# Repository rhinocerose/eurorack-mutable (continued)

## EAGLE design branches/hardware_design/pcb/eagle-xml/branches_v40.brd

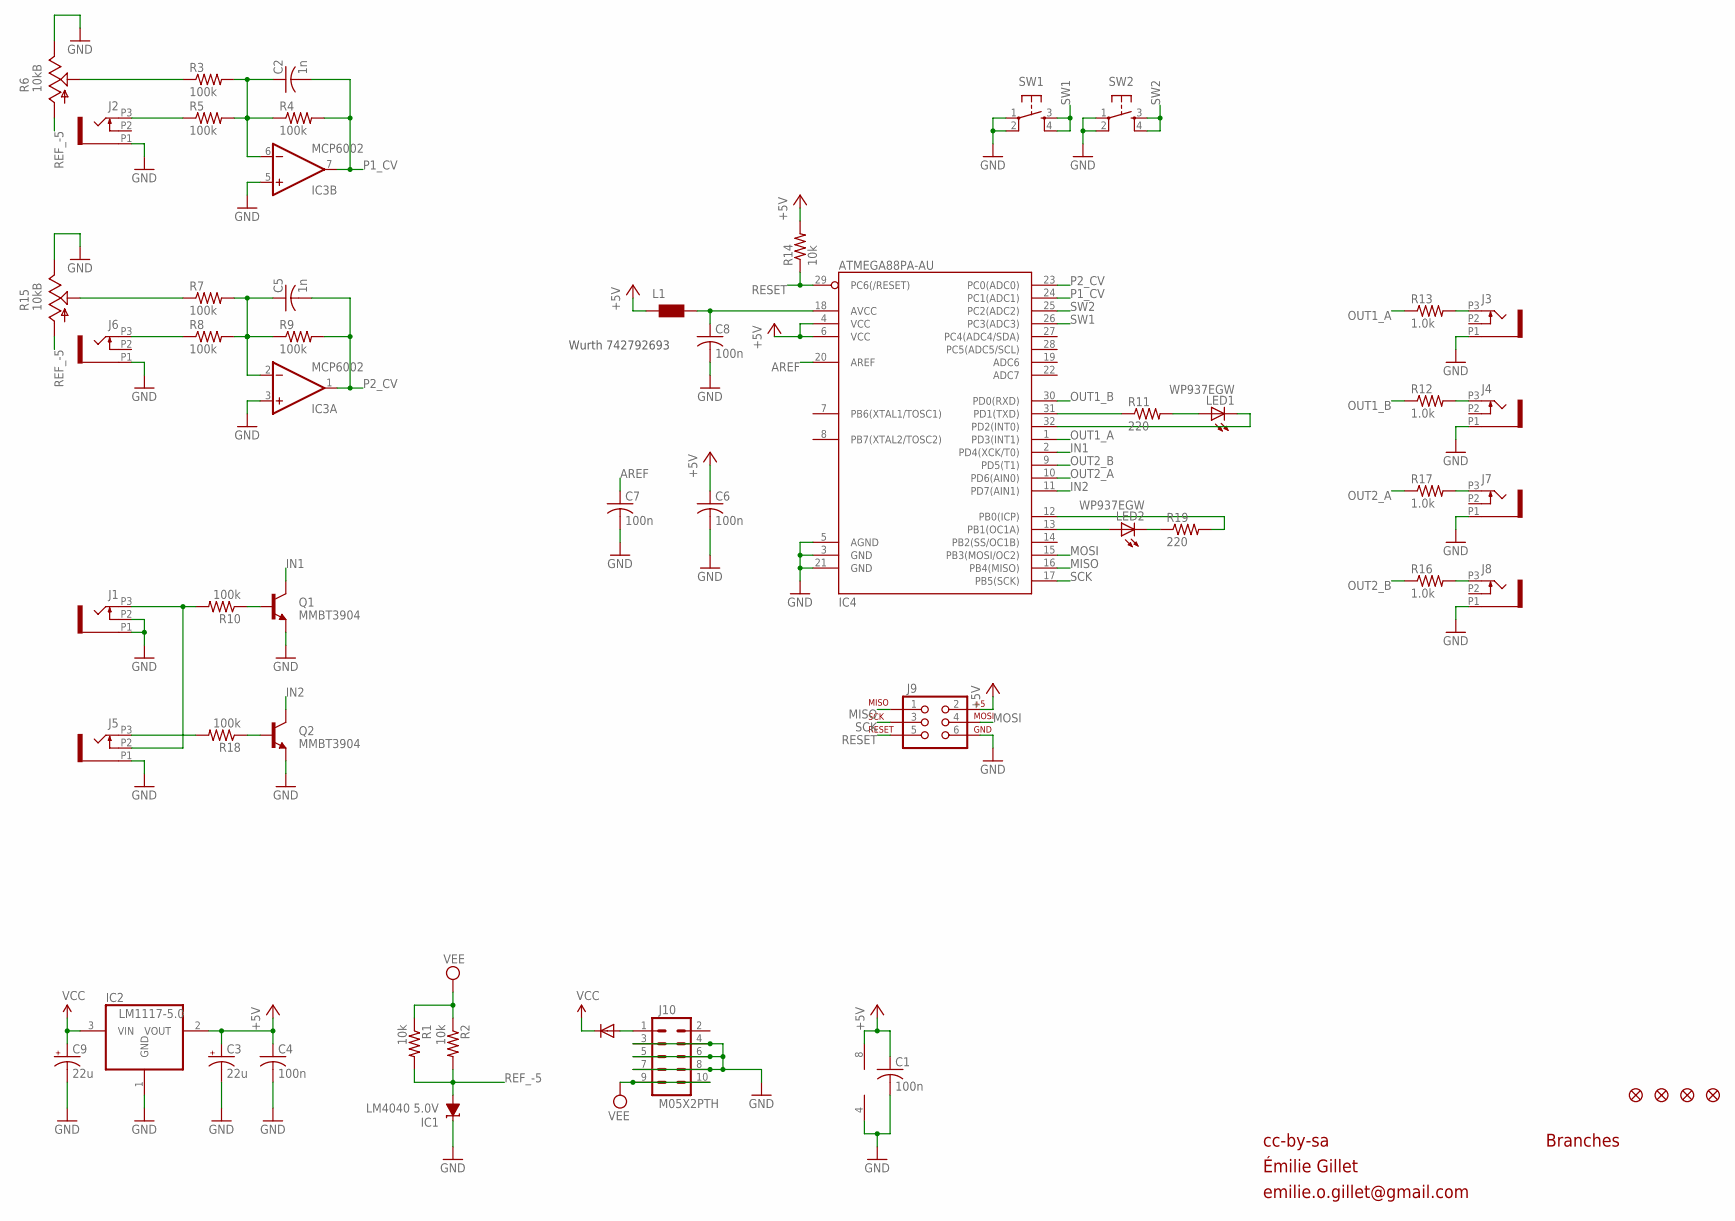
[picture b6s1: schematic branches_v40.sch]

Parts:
C1, C4, C6, C7, C8: 100n; C0603
C2, C5: 1n; C0603
C3, C9: 22u; PANASONIC_C
D1: 1N5819HW; SOD123
F1, F2, F3, F4: FIDUCIAL1X2; FIDUCIAL-1X2
IC1: LM4040 5.0V; DBZ_R-PDSO-G3
IC2: LM1117-5.0; SOT223
IC3: MCP6002; SO08
IC4: ATMEGA88PA-AU; TQFP32-08
J1, J2, J3, J4, J5, J6, J7, J8: PJ301_THONKICONN6; WQP_PJ_301M6
J9: AVR_SPI_PRG_6PTH; 2X3
J10: M05X2PTH; AVR_ICSP
L1: WE-CBF_0603; 0603
LED1, LED2: WP937EGW; LED3MM
Q1, Q2: MMBT3904; SOT23-BEC
R1, R2, R14: 10k; R0603
R3, R4, R5, R7, R8, R9, R10, R18: 100k; R0603
R6, R15: 10kB; ALPS_POT_VERTICAL_PS
R11, R19: 220; R0603
R12, R13, R16, R17: 1.0k; R0603
SW1, SW2: TAC_SWITCHPTH; TACTILE-PTH

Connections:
+5V: C1.1, C3.+, C4.1, C6.1, IC2.2 (VOUT), IC3.8 (V+), IC4.4 (VCC), IC4.6 (VCC), J9.2, L1.1, R14.2
AREF: C7.1, IC4.20 (AREF)
GATE1_IN: J1.P3 (3), J5.P2 (2), R10.2
GATE2_IN: J5.P3 (3), R18.2
GND: C1.2, C3.-, C4.2, C6.2, C7.2, C8.2, C9.-, IC1.1 (C), IC2.1 (GND), IC3.3 (+IN), IC3.4 (V-), IC3.5 (+IN), IC4.3 (GND), IC4.5 (AGND), IC4.21 (GND), J1.P1 (1), J1.P2 (2), J2.P1 (1), J3.P1 (1), J4.P1 (1), J5.P1 (1), J6.P1 (1), J7.P1 (1), J8.P1 (1), J9.6, J10.3, J10.4, J10.5, J10.6, J10.7, J10.8, Q1.E, Q2.E, R6.P$1 (E), R15.P$1 (E), SW1.1, SW1.2, SW2.1, SW2.2
IN1: IC4.2 (PD4(XCK/T0)), Q1.C
IN2: IC4.11 (PD7(AIN1)), Q2.C
MISO: IC4.16 (PB4(MISO)), J9.1
MOSI: IC4.15 (PB3(MOSI/OC2)), J9.4
unnamed: Q1.B, R10.1
unnamed: Q2.B, R18.1
unnamed: D1.A, J10.1
unnamed: C5.1, IC3.2 (-IN), R7.2, R8.2, R9.1
unnamed: J8.P3 (3), R16.2
unnamed: R7.1, R15.P$2 (S)
unnamed: R3.1, R6.P$2 (S)
unnamed: J2.P3 (3), R5.1
unnamed: J6.P3 (3), R8.1
unnamed: IC4.31 (PD1(TXD)), R11.1
unnamed: LED1.A, R11.2
unnamed: IC4.32 (PD2(INT0)), LED1.K (C)
unnamed: IC4.13 (PB1(OC1A)), LED2.A
unnamed: LED2.K (C), R19.1
unnamed: IC4.12 (PB0(ICP)), R19.2
unnamed: C2.1, IC3.6 (-IN), R3.2, R4.1, R5.2
unnamed: J3.P3 (3), R13.2
unnamed: J4.P3 (3), R12.2
unnamed: J7.P3 (3), R17.2
unnamed: C8.1, IC4.18 (AVCC), L1.2
OUT1_A: IC4.1 (PD3(INT1)), R13.1
OUT1_B: IC4.30 (PD0(RXD)), R12.1
OUT2_A: IC4.10 (PD6(AIN0)), R17.1
OUT2_B: IC4.9 (PD5(T1)), R16.1
P1_CV: C2.2, IC3.7 (OUT), IC4.24 (PC1(ADC1)), R4.2
P2_CV: C5.2, IC3.1 (OUT), IC4.23 (PC0(ADC0)), R9.2
REF_-5: IC1.2 (A), R1.2, R2.2, R6.P$3 (A), R15.P$3 (A)
RESET: IC4.29 (PC6(/RESET)), J9.5, R14.1
SCK: IC4.17 (PB5(SCK)), J9.3
SW1: IC4.26 (PC3(ADC3)), SW1.3, SW1.4
SW2: IC4.25 (PC2(ADC2)), SW2.3, SW2.4
VCC: C9.+, D1.C, IC2.3 (VIN)
VEE: J10.9, J10.10, R1.1, R2.1

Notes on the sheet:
cc-by-sa
Branches
Wurth 742792693
Émilie Gillet
emilie.o.gillet@gmail.com

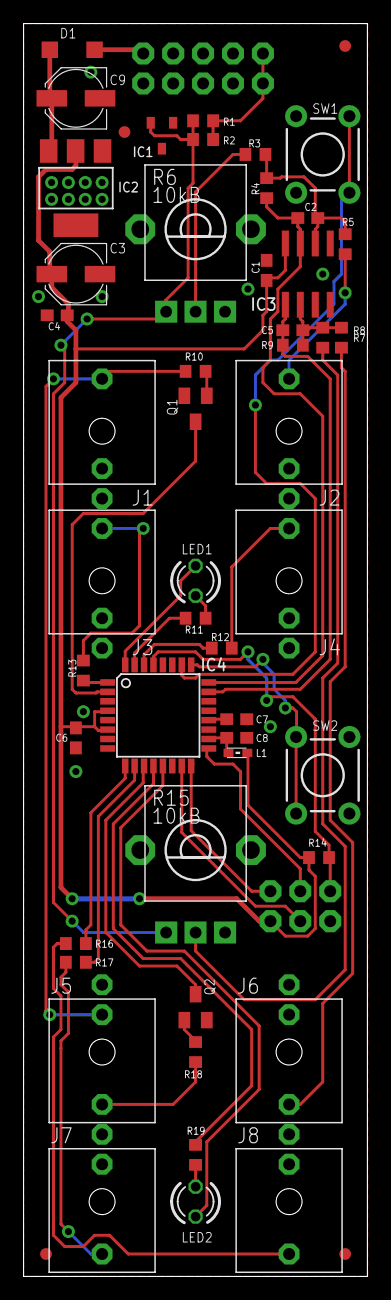
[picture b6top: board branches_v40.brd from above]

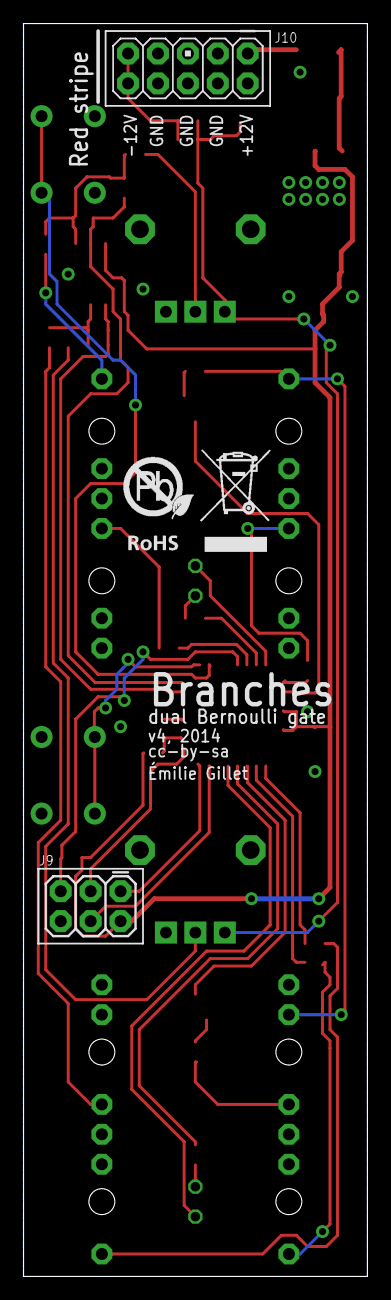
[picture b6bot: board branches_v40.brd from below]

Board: 2 copper layers, 29.2 x 106.4 mm, 55 parts (3 on the bottom side), 42 nets.

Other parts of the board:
U$1: ROHS

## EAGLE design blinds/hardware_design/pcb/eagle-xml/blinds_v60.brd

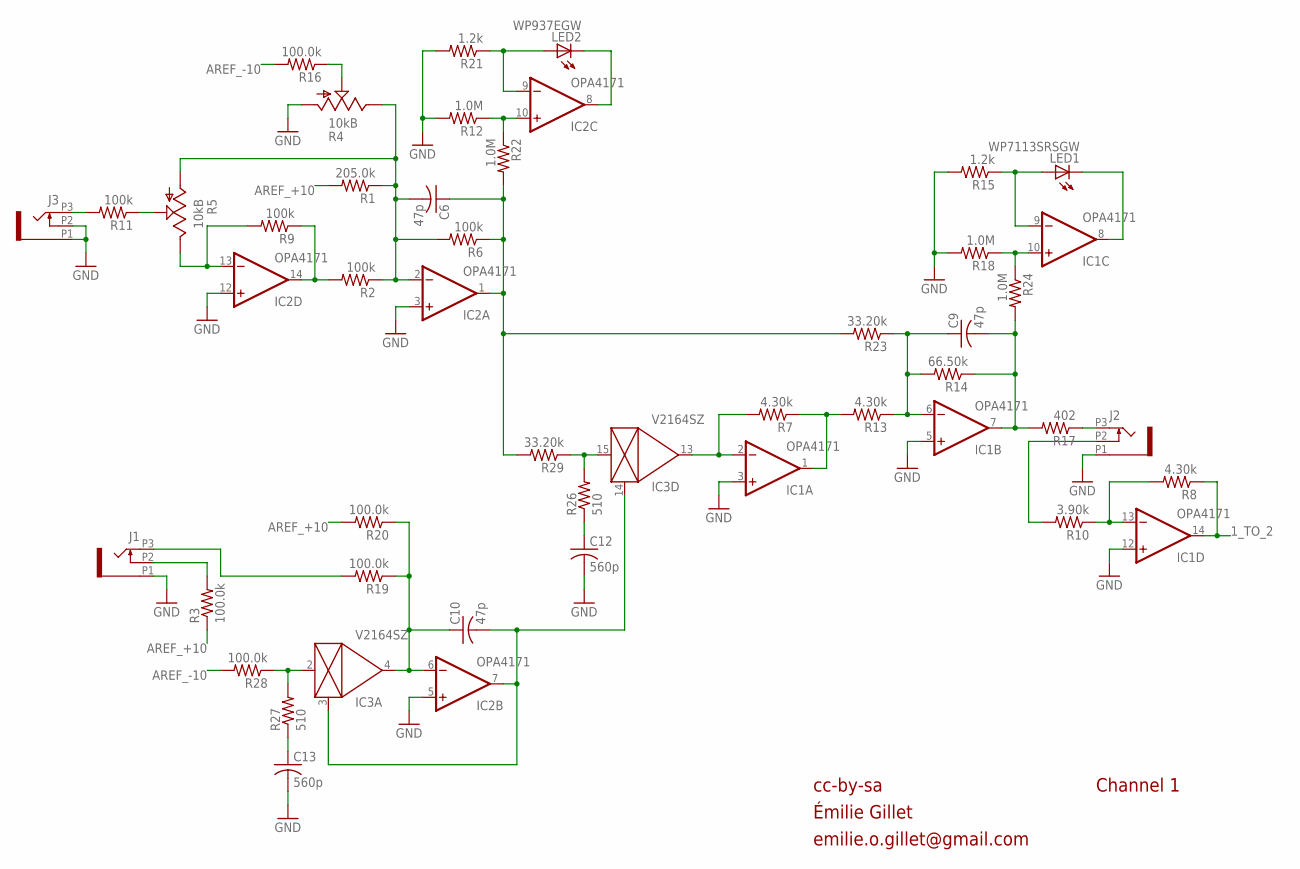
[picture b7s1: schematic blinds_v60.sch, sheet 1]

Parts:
C6, C9, C10: 47p; C0603
C12, C13: 560p; C0603
IC1, IC2: OPA4171; TSSOP14
IC3: V2164SZ; SOIC16N
J1, J2, J3: PJ301_THONKICONN6; WQP_PJ_301M6
LED1: WP7113SRSGW; LED5MM
LED2: WP937EGW; LED3MM
R1: 205.0k; R0603
R2, R6, R9, R11: 100k; R0603
R3, R16, R19, R20, R28: 100.0k; R0603
R4: 10kB; ALPS_POT_VERTICAL_PS
R5: 10kB; ALPS_POT_VERTICAL
R7, R8, R13: 4.30k; R0603
R10: 3.90k; R0603
R12, R18, R22, R24: 1.0M; R0603
R14: 66.50k; R0603
R15, R21: 1.2k; R0603
R17: 402; R0603
R23, R29: 33.20k; R0603
R26, R27: 510; R0603

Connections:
1_TO_2: IC1.14 (OUT), R8.1; also elsewhere on the board
AREF_+10: R1.2, R3.1, R20.2; also elsewhere on the board
AREF_-10: R16.2, R28.2; also elsewhere on the board
CV_IN_1: J3.P3 (3), R11.2
FOO: IC3.2 (IN), R27.2, R28.1
GAIN_1: C6.1, IC2.1 (OUT), R6.1, R22.2, R23.2, R29.2
GND: C12.2, C13.2, IC1.3 (+IN), IC1.5 (+IN), IC1.12 (+IN), IC2.3 (+IN), IC2.5 (+IN), IC2.12 (+IN), J1.P1 (1), J2.P1 (1), J3.P1 (1), J3.P2 (2), R4.P$3 (A), R12.2, R15.2, R18.2, R21.2; also elsewhere on the board
unnamed: R4.P$2 (S), R16.1
unnamed: IC1.2 (-IN), IC3.13 (OUT), R7.2
unnamed: IC2.8 (OUT), LED2.K (C)
unnamed: IC2.13 (-IN), R5.P$1 (E), R9.2
unnamed: J2.P3 (3), R17.1
unnamed: IC2.14 (OUT), R2.2, R9.1
unnamed: C6.2, IC2.2 (-IN), R1.1, R2.1, R4.P$1 (E), R5.P$3 (A), R6.2
unnamed: C9.1, IC1.6 (-IN), R13.1, R14.2, R23.1
unnamed: R5.P$2 (S), R11.1
unnamed: IC2.9 (-IN), LED2.A, R21.1
unnamed: IC1.8 (OUT), LED1.K (C)
unnamed: IC1.9 (-IN), LED1.A, R15.1
unnamed: C13.1, R27.1
unnamed: J1.P3 (3), R19.2
unnamed: IC1.13 (-IN), R8.2, R10.1
unnamed: J2.P2 (2), R10.2
unnamed: C12.1, R26.1
unnamed: J1.P2 (2), R3.2
unnamed: IC1.1 (OUT), R7.1, R13.2
unnamed: C10.1, IC2.6 (-IN), IC3.4 (OUT), R19.1, R20.1
unnamed: C10.2, IC2.7 (OUT), IC3.3 (CTRL), IC3.14 (CTRL)
unnamed: IC3.15 (IN), R26.2, R29.1
unnamed: IC1.10 (+IN), R18.1, R24.1
unnamed: IC2.10 (+IN), R12.1, R22.1
OUT1: C9.2, IC1.7 (OUT), R14.1, R17.2, R24.2

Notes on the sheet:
cc-by-sa
Émilie Gillet
emilie.o.gillet@gmail.com
Channel 1

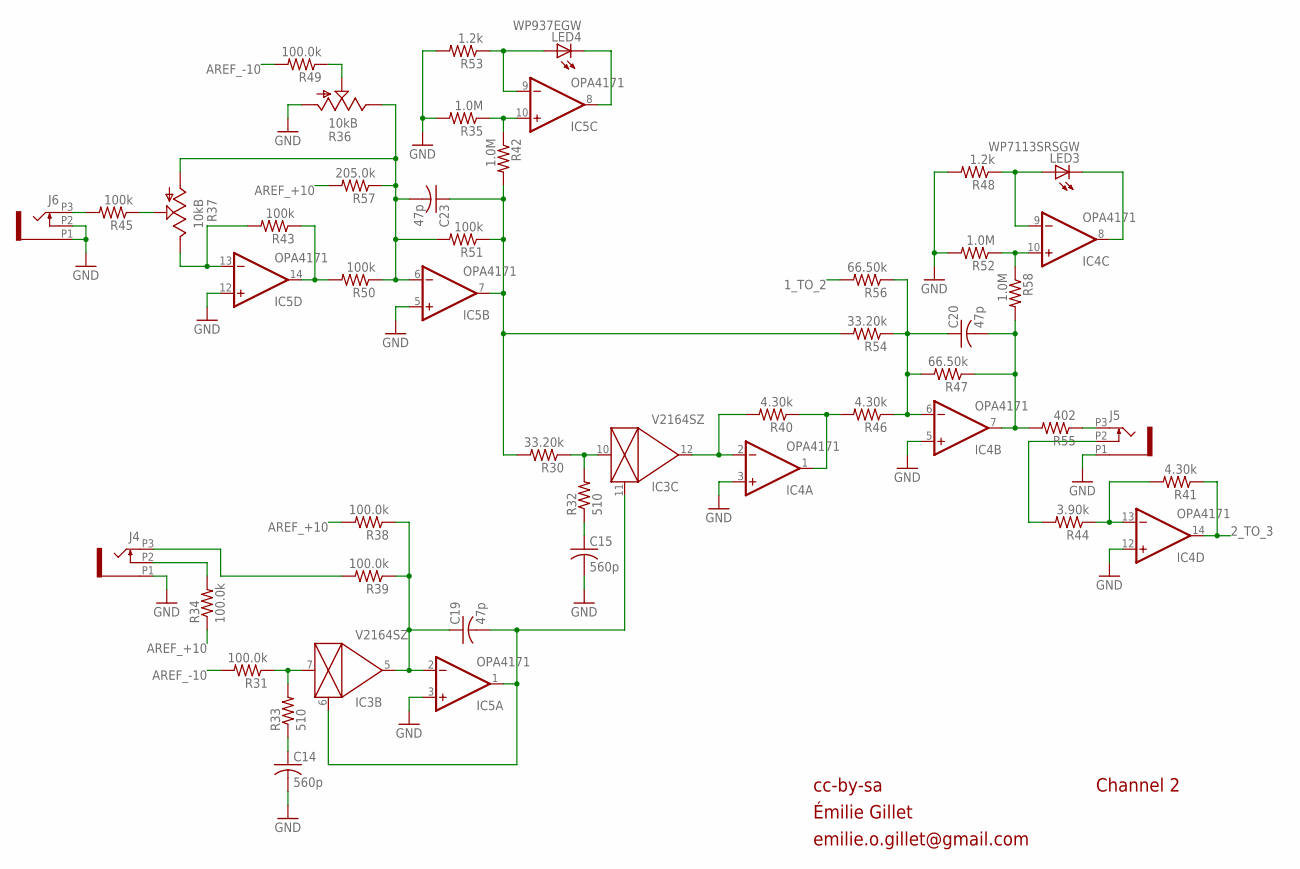
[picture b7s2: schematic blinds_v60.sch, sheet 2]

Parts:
C14, C15: 560p; C0603
C19, C20, C23: 47p; C0603
IC3: V2164SZ; SOIC16N
IC4, IC5: OPA4171; TSSOP14
J4, J5, J6: PJ301_THONKICONN6; WQP_PJ_301M6
LED3: WP7113SRSGW; LED5MM
LED4: WP937EGW; LED3MM
R30, R54: 33.20k; R0603
R31, R34, R38, R39, R49: 100.0k; R0603
R32, R33: 510; R0603
R35, R42, R52, R58: 1.0M; R0603
R36: 10kB; ALPS_POT_VERTICAL_PS
R37: 10kB; ALPS_POT_VERTICAL
R40, R41, R46: 4.30k; R0603
R43, R45, R50, R51: 100k; R0603
R44: 3.90k; R0603
R47, R56: 66.50k; R0603
R48, R53: 1.2k; R0603
R55: 402; R0603
R57: 205.0k; R0603

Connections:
1_TO_2: R56.2; also elsewhere on the board
2_TO_3: IC4.14 (OUT), R41.1; also elsewhere on the board
AREF_+10: R34.1, R38.2, R57.2; also elsewhere on the board
AREF_-10: R31.2, R49.2; also elsewhere on the board
FOO1: IC3.7 (IN), R31.1, R33.2
GAIN_2: C23.1, IC5.7 (OUT), R30.2, R42.2, R51.1, R54.2
GND: C14.2, C15.2, IC4.3 (+IN), IC4.5 (+IN), IC4.12 (+IN), IC5.3 (+IN), IC5.5 (+IN), IC5.12 (+IN), J4.P1 (1), J5.P1 (1), J6.P1 (1), J6.P2 (2), R35.2, R36.P$3 (A), R48.2, R52.2, R53.2; also elsewhere on the board
unnamed: J5.P3 (3), R55.1
unnamed: C15.1, R32.1
unnamed: IC3.10 (IN), R30.1, R32.2
unnamed: IC3.12 (OUT), IC4.2 (-IN), R40.2
unnamed: C20.1, IC4.6 (-IN), R46.1, R47.2, R54.1, R56.1
unnamed: J6.P3 (3), R45.2
unnamed: IC5.13 (-IN), R37.P$1 (E), R43.2
unnamed: IC5.14 (OUT), R43.1, R50.2
unnamed: C23.2, IC5.6 (-IN), R36.P$1 (E), R37.P$3 (A), R50.1, R51.2, R57.1
unnamed: R36.P$2 (S), R49.1
unnamed: IC5.8 (OUT), LED4.K (C)
unnamed: IC5.9 (-IN), LED4.A, R53.1
unnamed: IC4.8 (OUT), LED3.K (C)
unnamed: IC4.9 (-IN), LED3.A, R48.1
unnamed: IC4.13 (-IN), R41.2, R44.1
unnamed: J5.P2 (2), R44.2
unnamed: IC4.1 (OUT), R40.1, R46.2
unnamed: R37.P$2 (S), R45.1
unnamed: C14.1, R33.1
unnamed: C19.1, IC3.5 (OUT), IC5.2 (-IN), R38.1, R39.1
unnamed: C19.2, IC3.6 (CTRL), IC3.11 (CTRL), IC5.1 (OUT)
unnamed: J4.P3 (3), R39.2
unnamed: J4.P2 (2), R34.2
unnamed: IC4.10 (+IN), R52.1, R58.1
unnamed: IC5.10 (+IN), R35.1, R42.1
OUT2: C20.2, IC4.7 (OUT), R47.1, R55.2, R58.2

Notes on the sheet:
cc-by-sa
Channel 2
Émilie Gillet
emilie.o.gillet@gmail.com

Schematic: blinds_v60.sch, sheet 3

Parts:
C31, C34, C35: 47p; C0603
C37, C38: 560p; C0603
IC8, IC9: OPA4171; TSSOP14
IC10: V2164SZ; SOIC16N
J7, J8, J9: PJ301_THONKICONN6; WQP_PJ_301M6
LED5: WP7113SRSGW; LED5MM
LED6: WP937EGW; LED3MM
R61: 205.0k; R0603
R62, R66, R69, R71: 100k; R0603
R63, R76, R78, R79, R89: 100.0k; R0603
R64: 10kB; ALPS_POT_VERTICAL_PS
R65: 10kB; ALPS_POT_VERTICAL
R67, R68, R73: 4.30k; R0603
R70: 3.90k; R0603
R72, R77, R81, R85: 1.0M; R0603
R74, R82: 66.50k; R0603
R75, R80: 1.2k; R0603
R83, R90: 33.20k; R0603
R84: 402; R0603
R87, R88: 510; R0603

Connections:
2_TO_3: R82.2; also elsewhere on the board
3_TO_4: IC8.14 (OUT), R68.1; also elsewhere on the board
AREF_+10: R61.2, R63.1, R79.2; also elsewhere on the board
AREF_-10: R76.2, R89.2; also elsewhere on the board
FOO2: IC10.2 (IN), R88.2, R89.1
GAIN_3: C31.1, IC9.1 (OUT), R66.1, R81.2, R83.2, R90.2
GND: C37.2, C38.2, IC8.3 (+IN), IC8.5 (+IN), IC8.12 (+IN), IC9.3 (+IN), IC9.5 (+IN), IC9.12 (+IN), J7.P1 (1), J8.P1 (1), J9.P1 (1), J9.P2 (2), R64.P$3 (A), R72.2, R75.2, R77.2, R80.2; also elsewhere on the board
unnamed: J8.P3 (3), R84.1
unnamed: C37.1, R87.1
unnamed: IC10.15 (IN), R87.2, R90.1
unnamed: IC8.2 (-IN), IC10.13 (OUT), R67.2
unnamed: C34.1, IC8.6 (-IN), R73.1, R74.2, R82.1, R83.1
unnamed: J9.P3 (3), R71.2
unnamed: IC9.13 (-IN), R65.P$1 (E), R69.2
unnamed: IC9.14 (OUT), R62.2, R69.1
unnamed: C31.2, IC9.2 (-IN), R61.1, R62.1, R64.P$1 (E), R65.P$3 (A), R66.2
unnamed: R64.P$2 (S), R76.1
unnamed: IC9.8 (OUT), LED6.K (C)
unnamed: IC9.9 (-IN), LED6.A, R80.1
unnamed: IC8.8 (OUT), LED5.K (C)
unnamed: IC8.9 (-IN), LED5.A, R75.1
unnamed: IC8.13 (-IN), R68.2, R70.1
unnamed: J8.P2 (2), R70.2
unnamed: IC8.1 (OUT), R67.1, R73.2
unnamed: C38.1, R88.1
unnamed: C35.1, IC9.6 (-IN), IC10.4 (OUT), R78.1, R79.1
unnamed: C35.2, IC9.7 (OUT), IC10.3 (CTRL), IC10.14 (CTRL)
unnamed: R65.P$2 (S), R71.1
unnamed: J7.P3 (3), R78.2
unnamed: J7.P2 (2), R63.2
unnamed: IC8.10 (+IN), R77.1, R85.1
unnamed: IC9.10 (+IN), R72.1, R81.1
OUT3: C34.2, IC8.7 (OUT), R74.1, R84.2, R85.2

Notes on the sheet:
cc-by-sa
Channel 3
Émilie Gillet
emilie.o.gillet@gmail.com

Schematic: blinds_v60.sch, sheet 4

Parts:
C39, C40: 560p; C0603
C44, C45, C48: 47p; C0603
IC10: V2164SZ; SOIC16N
IC11, IC12: OPA4171; TSSOP14
J10, J11, J12: PJ301_THONKICONN6; WQP_PJ_301M6
LED7: WP7113SRSGW; LED5MM
LED8: WP937EGW; LED3MM
R91, R103: 33.20k; R0603
R92, R95, R101, R102, R109: 100.0k; R0603
R93, R94: 510; R0603
R96, R104, R110, R115: 1.0M; R0603
R97: 10kB; ALPS_POT_VERTICAL_PS
R98: 10kB; ALPS_POT_VERTICAL
R99, R100: 4.30k; R0603
R105, R106, R111, R112: 100k; R0603
R107, R114: 66.50k; R0603
R108, R113: 1.2k; R0603
R116: 402; R0603
R117: 205.0k; R0603

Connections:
3_TO_4: R114.2; also elsewhere on the board
AREF_+5: IC11.13 (-IN), IC11.14 (OUT)
AREF_+10: R95.1, R101.2, R117.2; also elsewhere on the board
AREF_-10: R92.2, R109.2; also elsewhere on the board
FOO3: IC10.7 (IN), R92.1, R94.2
GAIN_4: C48.1, IC12.7 (OUT), R91.2, R103.2, R104.2, R112.1
GND: C39.2, C40.2, IC11.3 (+IN), IC11.5 (+IN), IC11.12 (+IN), IC12.3 (+IN), IC12.5 (+IN), IC12.12 (+IN), J10.P1 (1), J11.P1 (1), J12.P1 (1), J12.P2 (2), R96.2, R97.P$3 (A), R108.2, R110.2, R113.2; also elsewhere on the board
unnamed: J10.P3 (3), R102.2
unnamed: J11.P3 (3), R116.1
unnamed: C40.1, R93.1
unnamed: IC10.10 (IN), R91.1, R93.2
unnamed: IC10.12 (OUT), IC11.2 (-IN), R100.2
unnamed: C45.1, IC11.6 (-IN), R99.1, R103.1, R107.2, R114.1
unnamed: J12.P3 (3), R106.2
unnamed: IC12.13 (-IN), R98.P$1 (E), R105.2
unnamed: IC12.14 (OUT), R105.1, R111.2
unnamed: C48.2, IC12.6 (-IN), R97.P$1 (E), R98.P$3 (A), R111.1, R112.2, R117.1
unnamed: R97.P$2 (S), R109.1
unnamed: IC12.8 (OUT), LED8.K (C)
unnamed: IC12.9 (-IN), LED8.A, R113.1
unnamed: IC11.8 (OUT), LED7.K (C)
unnamed: IC11.9 (-IN), LED7.A, R108.1
unnamed: IC11.1 (OUT), R99.2, R100.1
unnamed: R98.P$2 (S), R106.1
unnamed: C39.1, R94.1
unnamed: C44.1, IC10.5 (OUT), IC12.2 (-IN), R101.1, R102.1
unnamed: C44.2, IC10.6 (CTRL), IC10.11 (CTRL), IC12.1 (OUT)
unnamed: J10.P2 (2), R95.2
unnamed: IC11.10 (+IN), R110.1, R115.1
unnamed: IC12.10 (+IN), R96.1, R104.1
OUT4: C45.2, IC11.7 (OUT), R107.1, R115.2, R116.2

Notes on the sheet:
cc-by-sa
Channel 4
Émilie Gillet
emilie.o.gillet@gmail.com

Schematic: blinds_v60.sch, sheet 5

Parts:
C1, C2: 22u; PANASONIC_C
C3, C4, C5, C7, C8, C11, C16, C17, C18, C21, C22, C24, C25, C26, C27, C28, C29, C30, C32, C33, C36, C41, C42, C43, C46, C47: 100n; C0603
D1, D2: 1N5819HW; SOD123
IC1, IC2, IC4, IC5, IC8, IC9, IC11, IC12: OPA4171; TSSOP14
IC3, IC10: V2164SZ; SOIC16N
IC6, IC7: LM4040B10; DBZ_R-PDSO-G3
JP1, JP2, JP3, JP4: FIDUCIAL1X2; FIDUCIAL-1X2
JP5: M05X2PTH; AVR_ICSP
L1, L2: WE-CBF_0603; 0603
P1: PTCSMD; PTC-1206
R25, R86: DNP; R0603
R59, R60: 1.2k; R0603

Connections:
AREF_+10: C3.1, C26.1, C28.1, IC6.1 (C), R59.2; also elsewhere on the board
AREF_-10: C27.1, IC7.2 (A), R60.2; also elsewhere on the board
GND: C1.+, C2.-, C3.2, C4.1, C5.2, C7.2, C8.1, C11.2, C16.1, C17.1, C18.2, C21.2, C22.1, C24.2, C25.2, C26.2, C27.2, C28.2, C29.1, C30.2, C32.2, C33.1, C36.2, C41.1, C42.1, C43.2, C46.2, C47.1, D1.C, IC3.8 (GND), IC6.2 (A), IC7.1 (C), IC10.8 (GND), JP5.3, JP5.4, JP5.5, JP5.6, JP5.7, JP5.8; also elsewhere on the board
unnamed: IC3.1 (MODE), R25.2
unnamed: D2.A, JP5.1, JP5.2
unnamed: JP5.9, JP5.10, P1.2
unnamed: L2.2, P1.1
unnamed: D2.C, L1.2
unnamed: IC10.1 (MODE), R86.2
VCC: C2.+, C5.1, C7.1, C11.1, C18.1, C21.1, C24.1, C30.1, C32.1, C36.1, C43.1, C46.1, IC1.4 (V+), IC2.4 (V+), IC3.16 (V+), IC4.4 (V+), IC5.4 (V+), IC8.4 (V+), IC9.4 (V+), IC10.16 (V+), IC11.4 (V+), IC12.4 (V+), L1.1, R25.1, R59.1, R86.1
VEE: C1.-, C4.2, C8.2, C16.2, C17.2, C22.2, C25.1, C29.2, C33.2, C41.2, C42.2, C47.2, D1.A, IC1.11 (V-), IC2.11 (V-), IC3.9 (V-), IC4.11 (V-), IC5.11 (V-), IC8.11 (V-), IC9.11 (V-), IC10.9 (V-), IC11.11 (V-), IC12.11 (V-), L2.1, R60.1

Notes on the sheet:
cc-by-sa
Power supply
1.2mA delivered
0.8mA needed
Émilie Gillet
emilie.o.gillet@gmail.com

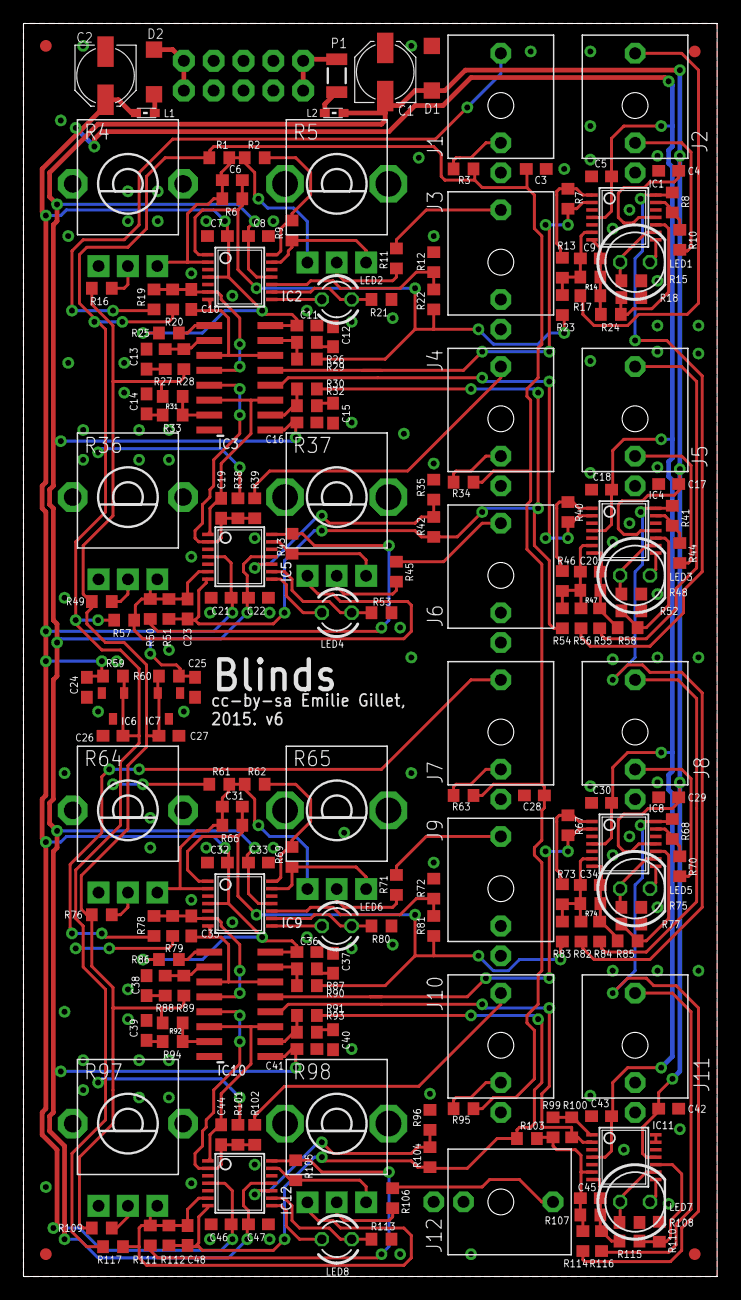
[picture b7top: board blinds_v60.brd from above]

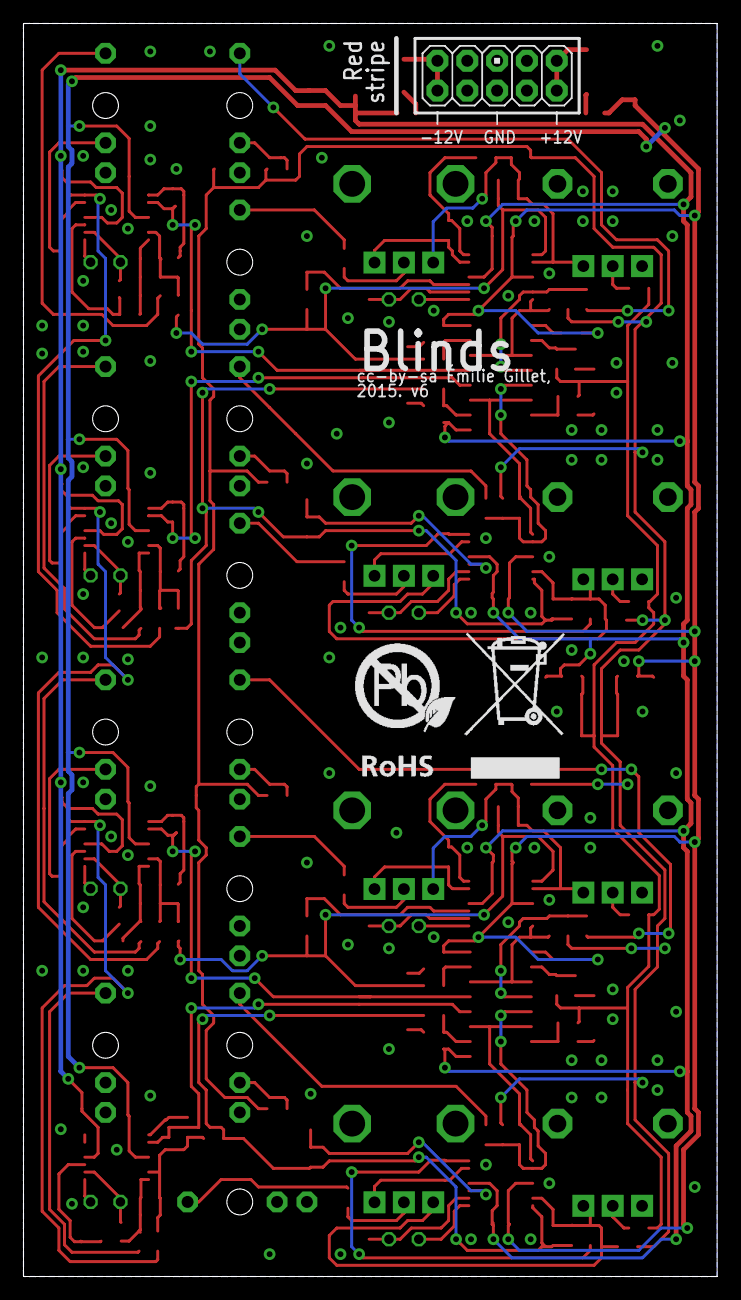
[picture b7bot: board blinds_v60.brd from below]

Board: 2 copper layers, 59.1 x 106.7 mm, 208 parts (2 on the bottom side), 125 nets.

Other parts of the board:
U$2: ROHS_BIG

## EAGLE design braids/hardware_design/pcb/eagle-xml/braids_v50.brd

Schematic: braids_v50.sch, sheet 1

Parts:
C1, C2, C3, C5, C7, C11, C31: 100n; C0603
C6, C12: 1u; C0603
C9, C10: 18p; C0603
DISP1, DISP2: KINGBRIGHT-PDC54-11; PDC54
IC1, IC2: 74HC595D; SO16
IC4: MCP3204; SO14
IC5: DAC8551; MSOP-8
JP2: M05X2MINIJTAG; 2X5-1.27
JP3: M06SIP; 1X06
Q1, Q2, Q3, Q4: MMBT3904; SOT23-BEC
Q5: 8MHz; HC49UP
R1, R2, R3, R11: 1.0k; R0603
R4, R5, R6, R7, R8, R9, R10, R12, R13, R14, R15, R16, R17, R18: 100; R0603
R19: 10kB; ALPS_POT_VERTICAL_PS
R22, R33: 10k; R0603
SW1: EC12E_SW; ALPS_EC12E_SW
SW2, SW3: EVQQ2; EVQ-Q2
UC1: STM32F103CBT6; LQFP48

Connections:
+3V3: C1.1, C2.1, C3.1, C5.1, C6.1, C7.1, C11.1, C12.1, IC1.10 (SCL), IC1.16 (VCC), IC2.10 (SCL), IC2.16 (VCC), IC4.14 (VDD), IC5.1 (VDD), JP2.1, R19.P$1 (E), R22.2, SW3.B (S), SW3.B' (S1), UC1.1 (VBAT), UC1.9 (VDD_A), UC1.24 (VDD_1), UC1.36 (VDD_2), UC1.48 (VDD_3); also elsewhere on the board
ADC_MISO: IC4.10 (DOUT), UC1.16 (PA6/SPI1_MISO/ADC12_IN6/TIM3_CH1)
ADC_MOSI: IC4.9 (DIN), UC1.17 (PA7/SPI1_MOSI/ADC12_IN7/TIM3_CH2)
ADC_SCK: IC4.11 (CLK), UC1.15 (PA5/SPI1_SCK/ADC12_IN5)
ADC_SS: IC4.8 (!CS), UC1.18 (PB0/ADC12_IN8/TIM3_CH3)
AREF: IC4.13 (VREF), IC5.2 (VREF); also elsewhere on the board
AUDIO_OUT: IC5.3 (FB), IC5.4 (OUT); also elsewhere on the board
BOOT_FLASH: R33.2, SW3.A, SW3.A' (P1), UC1.44 (BOOT0)
DAC_MOSI: IC5.7 (DIN), UC1.28 (PB15/SPI2_MOSI/TIM1_CH3N)
DAC_SCK: IC5.6 (SCLK), UC1.26 (PB13/SPI2_SCK/USART3_CTS/TIM1_CH1N)
DAC_SS: IC5.5 (!SYNC), UC1.25 (PB12/SPI2_NSS/I2C2_SMBA/USART3_CK/TIM1_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)
DISP_CHAR0: R3.1, UC1.43 (PB7/I2C1_SDA/TIM4_CH2)
DISP_CHAR1: R11.1, UC1.45 (PB8/TIM4_CH3)
DISP_CHAR2: R1.1, UC1.41 (PB5/I2C1_SMBA)
DISP_CHAR3: R2.1, UC1.42 (PB6/I2C1_SCL/TIM4_CH1)
DISP_EN: IC1.12 (RCK), IC2.12 (RCK), UC1.21 (PB10/I2C2_SCL/USART3_TX)
DISP_SCK: IC1.11 (SCK), IC2.11 (SCK), UC1.22 (PB11/I2C2_SDA/USART3_RX)
DISP_SER: IC2.14 (SER), UC1.19 (PB1/ADC12_IN9/TIM3_CH4)
ENC_A: SW1.B, UC1.3 (PC14-OSC32_IN)
ENC_B: SW1.A, UC1.4 (PC15-OSC32_OUT)
ENC_CLICK: SW1.E (2), UC1.2 (PC13-TAMPER-RTC)
FINE_TUNE: C31.1, R19.P$2 (S), UC1.13 (PA3/USART2_RX/ADC12_IN3/TIM2_CH4)
FM_CV: IC4.4 (CH3); also elsewhere on the board
GATE: UC1.14 (PA4/SPI1_NSS/USART2_CK/ADC12_IN4); also elsewhere on the board
GND: C1.2, C2.2, C3.2, C5.2, C6.2, C7.2, C9.1, C10.1, C11.2, C12.2, C31.2, IC1.8 (GND), IC1.13 (G), IC2.8 (GND), IC2.13 (G), IC4.7 (DGND), IC4.12 (AGND), IC5.8 (GND), JP2.3, JP2.5, JP2.9, JP3.1, Q1.E, Q2.E, Q3.E, Q4.E, R19.P$3 (A), R33.1, SW1.C, SW1.D (1), SW2.A, SW2.A' (P1), UC1.8 (VSS_A), UC1.20 (PB2/BOOT1), UC1.23 (VSS_1), UC1.35 (VSS_2), UC1.46 (PB9/TIM4_CH4), UC1.47 (VSS_3); also elsewhere on the board
JTCK: JP2.4, UC1.37 (PA14/JTCK/SWCLK)
JTDI: JP2.8, UC1.38 (PA15/JTDI)
JTDO: JP2.6, UC1.39 (PB3/JTDO)
JTMS: JP2.2, UC1.34 (PA13/JTMS/SWDIO)
unnamed: DISP2.16 (K1), Q3.C
unnamed: DISP2.11 (K2), Q4.C
unnamed: DISP1.16 (K1), Q1.C
unnamed: DISP1.11 (K2), Q2.C
unnamed: Q3.B, R3.2
unnamed: Q4.B, R11.2
unnamed: C9.2, Q5.2, UC1.5 (PD0-OSC_IN)
unnamed: C10.2, Q5.1, UC1.6 (PD1-OSC_OUT)
unnamed: Q1.B, R1.2
unnamed: Q2.B, R2.2
unnamed: DISP1.12 (A), DISP2.12 (A), R9.2
unnamed: DISP1.10 (B), DISP2.10 (B), R10.2
unnamed: DISP1.9 (C), DISP2.9 (C), R12.2
unnamed: DISP1.7 (D), DISP2.7 (D), R18.2
unnamed: DISP1.1 (E), DISP2.1 (E), R13.2
unnamed: DISP1.18 (F), DISP2.18 (F), R4.2
unnamed: DISP1.17 (G), DISP2.17 (G), R5.2
unnamed: DISP1.15 (H), DISP2.15 (H), R6.2
unnamed: DISP1.14 (J), DISP2.14 (J), R7.2
unnamed: DISP1.6 (K), DISP2.6 (K), R17.2
unnamed: DISP1.5 (L), DISP2.5 (L), R16.2
unnamed: DISP1.4 (M), DISP2.4 (M), R15.2
unnamed: DISP1.2 (N), DISP2.2 (N), R14.2
unnamed: DISP1.13, DISP2.13, R8.2
unnamed: IC2.7 (QH), R6.1
unnamed: IC1.14 (SER), IC2.9 (QH*)
unnamed: IC2.15 (QA), R9.1
unnamed: IC2.1 (QB), R10.1
unnamed: IC2.2 (QC), R12.1
unnamed: IC2.3 (QD), R18.1
unnamed: IC2.4 (QE), R13.1
unnamed: IC2.5 (QF), R4.1
unnamed: IC2.6 (QG), R5.1
unnamed: IC1.15 (QA), R7.1
unnamed: IC1.1 (QB), R17.1
unnamed: IC1.2 (QC), R16.1
unnamed: IC1.3 (QD), R15.1
unnamed: IC1.4 (QE), R14.1
unnamed: IC1.5 (QF), R8.1
PARAM1_CV: IC4.1 (CH0); also elsewhere on the board
PARAM2_CV: IC4.2 (CH1); also elsewhere on the board
PITCH_CV: IC4.3 (CH2); also elsewhere on the board
RESET: JP2.10, R22.1, SW2.B (S), SW2.B' (S1), UC1.7 (NRST)
RX: JP3.4, UC1.31 (PA10/USART1_RX/TIM1_CH3)
TX: JP3.5, UC1.30 (PA9/USART1_TX/TIM1_CH2)

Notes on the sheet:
cc-by-sa
Serial / System Bootloader
mini JTAG
Digital section
grounded on v4.0 or above
Émilie Gillet
emilie.o.gillet@gmail.com

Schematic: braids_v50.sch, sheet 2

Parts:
C13, C14, C16, C17: 1n; C0603
C18, C20, C23, C27, C28: 100n; C0603
C21, C22: 100p; C0603
C24: 10u; PANASONIC_B
C29: 47p; C0603
IC7: MCP6004; SO14
IC9: TL074D; SO14
IC10: TL072; SO08
J1, J2, J3, J4, J5, J6: PJ301_THONKICONN6; WQP_PJ_301M6
Q6: MMBT3904; SOT23-BEC
R20, R21, R36, R37, R38: 10kB; ALPS_POT_VERTICAL_PS
R24, R29, R47, R48, R54, R56: 100k; R0603
R25, R26: 49.9k; R0603
R27: 10k; R0603
R28, R32, R40: 200k; R0603
R30, R31, R34, R35, R41, R42, R43, R44, R50, R52, R53: 24.9k; R0603
R39: 120k; R0603
R45, R46: 39k; R0603
R55: 1.0k; R0603

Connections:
+3V3: C18.1, IC7.4 (V+), R27.2; also elsewhere on the board
AREF_-10: R20.P$1 (E), R36.P$1 (E), R38.P$1 (E), R40.1; also elsewhere on the board
AUDIO_OUT: R45.2; also elsewhere on the board
FM_CV: C17.2, IC7.7 (OUT), R35.2; also elsewhere on the board
GATE: Q6.C, R27.1; also elsewhere on the board
GND: C18.2, C20.1, C22.2, C23.2, C27.1, C28.2, IC7.3 (+IN), IC7.5 (+IN), IC7.10 (+IN), IC7.11 (V-), IC7.12 (+IN), IC9.3 (+IN), IC9.5 (+IN), IC9.10 (+IN), IC9.12 (+IN), IC10.3 (+IN), J1.P1 (1), J2.P1 (1), J3.P1 (1), J4.P1 (1), J5.P1 (1), J6.P1 (1), Q6.E, R20.P$3 (A), R36.P$3 (A), R38.P$3 (A); also elsewhere on the board
unnamed: IC9.7 (OUT), R41.1, R53.2
unnamed: R20.P$2 (S), R39.1
unnamed: J2.P3 (3), R54.1
unnamed: C16.1, IC7.2 (-IN), R34.1, R39.2, R41.2
unnamed: IC9.6 (-IN), R53.1, R54.2
unnamed: J3.P3 (3), R24.1
unnamed: J4.P3 (3), R48.1
unnamed: R21.P$2 (S), R24.2
unnamed: IC9.13 (-IN), R37.P$1 (E), R43.1
unnamed: IC9.14 (OUT), R30.1, R43.2
unnamed: IC9.2 (-IN), R21.P$1 (E), R52.1
unnamed: IC9.1 (OUT), R42.1, R52.2
unnamed: C17.1, IC7.6 (-IN), R21.P$3 (A), R35.1, R40.2, R42.2
unnamed: J1.P3 (3), R29.1
unnamed: IC9.8 (OUT), R31.1, R44.2
unnamed: C13.1, IC7.13 (-IN), R25.1, R28.2, R30.2, R37.P$3 (A)
unnamed: J5.P3 (3), R47.1
unnamed: R28.1, R36.P$2 (S)
unnamed: R37.P$2 (S), R48.2
unnamed: IC9.9 (-IN), R44.1, R47.2
unnamed: R32.1, R38.P$2 (S)
unnamed: Q6.B, R29.2
unnamed: C21.2, C24.+, IC10.6 (-IN), IC10.7 (OUT)
unnamed: C24.-, R50.2
unnamed: C22.1, IC10.5 (+IN), R46.1
unnamed: C14.1, IC7.9 (-IN), R26.1, R31.2, R32.2
unnamed: C21.1, R45.1, R46.2
unnamed: J6.P3 (3), R55.1, R56.1
unnamed: C29.2, IC10.1 (OUT), R55.2
unnamed: C29.1, IC10.2 (-IN), R50.1, R56.2
PARAM1_CV: C13.2, IC7.14 (OUT), R25.2; also elsewhere on the board
PARAM2_CV: C14.2, IC7.8 (OUT), R26.2; also elsewhere on the board
PITCH_CV: C16.2, IC7.1 (OUT), R34.2; also elsewhere on the board
VCC: C23.1, C28.1, IC9.4 (V+), IC10.8 (V+); also elsewhere on the board
VEE: C20.2, C27.2, IC9.11 (V-), IC10.4 (V-); also elsewhere on the board

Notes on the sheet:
cc-by-sa
Analog Section
0 .. 2.5V
Émilie Gillet
emilie.o.gillet@gmail.com

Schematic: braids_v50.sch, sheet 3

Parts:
C4, C26: 100n; C0603
C8: 470n; C0603
C15, C19: 22u; PANASONIC_C
C25, C30: 47u; PANASONIC_D
D1, D2: 1N5819HW; SOD123
IC3: LM4040B25; DBZ_R-PDSO-G3
IC6: LM1117-3.3; TO252
IC8: LM4040B10; DBZ_R-PDSO-G3
JP1: M05X2PTH; AVR_ICSP
R23: 1.0k; R0603
R49: 4.7; R1206
R51: 330; R0603

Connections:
+3V3: C4.1, C15.+, IC6.3 (VOUT), R23.1; also elsewhere on the board
AREF: C8.1, IC3.1 (C), R23.2; also elsewhere on the board
AREF_-10: C26.1, IC8.2 (A), R51.2; also elsewhere on the board
GND: C4.2, C8.2, C15.-, C19.-, C25.-, C26.2, C30.+, IC3.2 (A), IC6.1 (GND), IC8.1 (C), JP1.3, JP1.4, JP1.5, JP1.6, JP1.7, JP1.8; also elsewhere on the board
unnamed: C19.+, IC6.2 (VIN), R49.1
unnamed: D1.A, JP1.1, JP1.2
unnamed: D2.C, JP1.9, JP1.10
VCC: C25.+, D1.C, R49.2; also elsewhere on the board
VEE: C30.-, D2.A, R51.1; also elsewhere on the board

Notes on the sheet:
3.5mA
200µA
cc-by-sa
Analog Section
Émilie Gillet
emilie.o.gillet@gmail.com

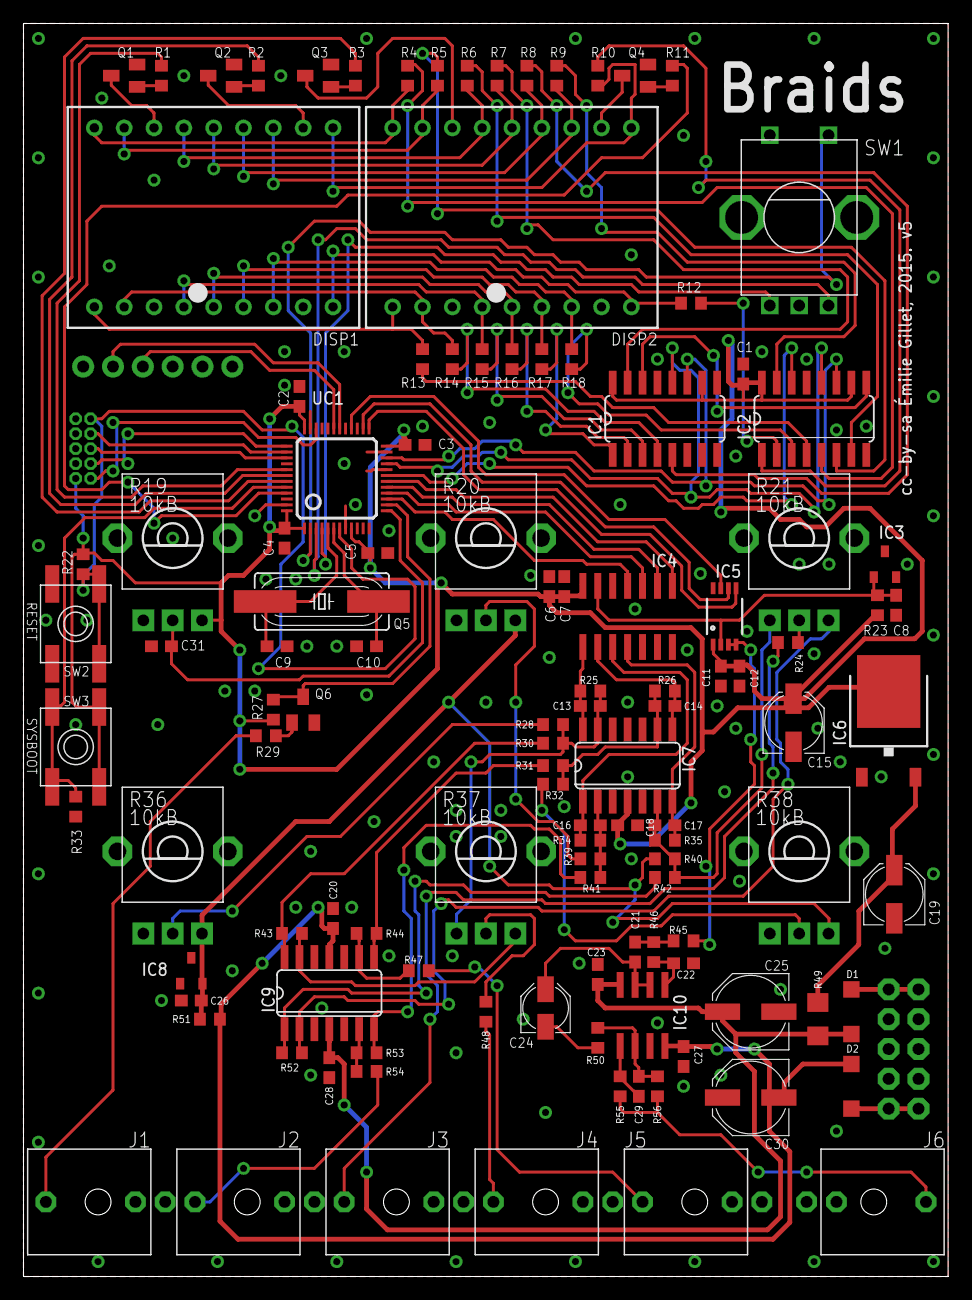
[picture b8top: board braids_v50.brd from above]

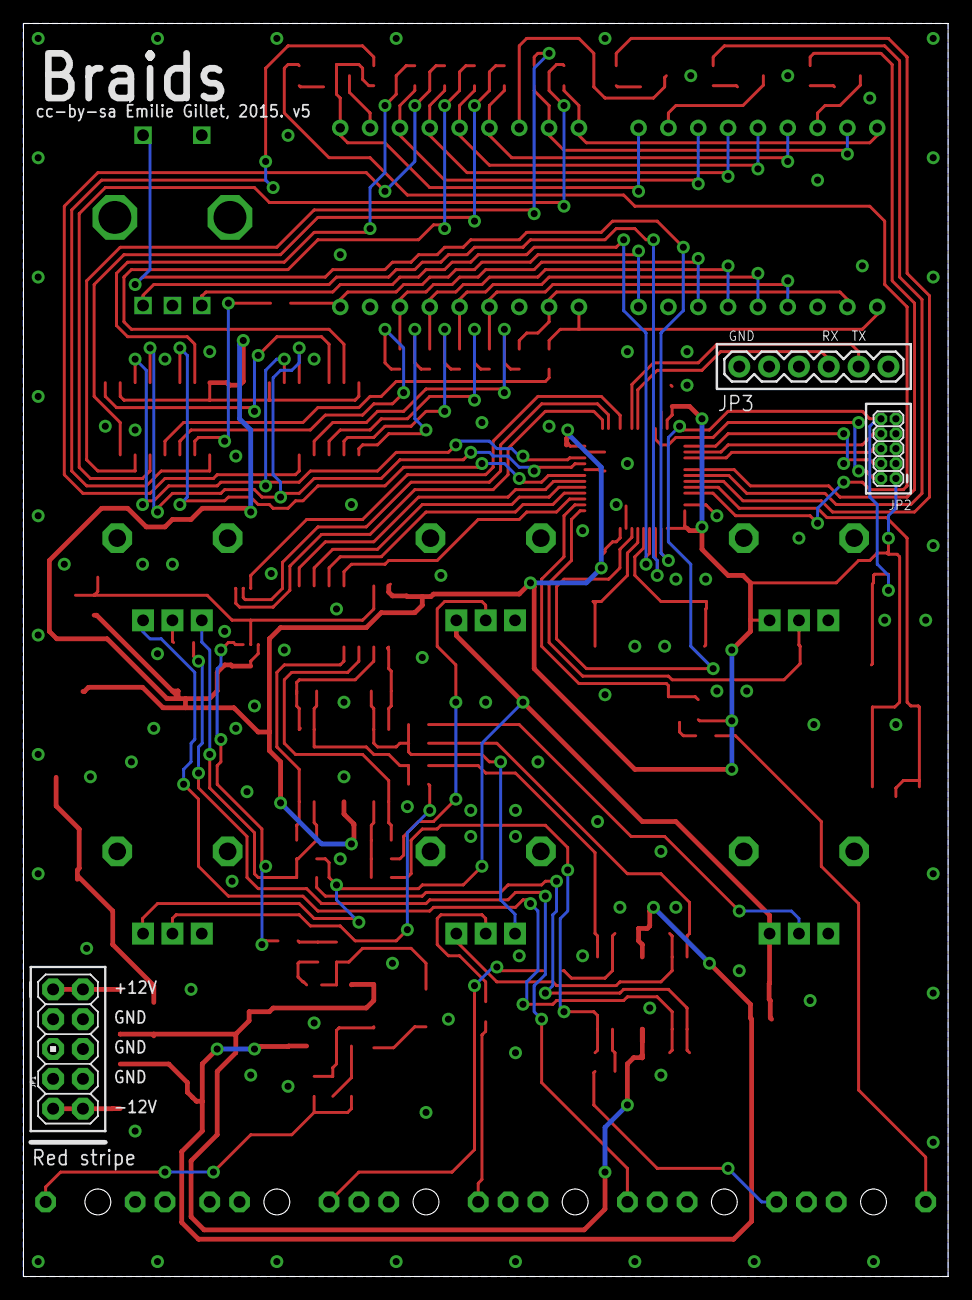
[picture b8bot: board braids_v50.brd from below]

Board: 2 copper layers, 78.7 x 106.7 mm, 120 parts (3 on the bottom side), 110 nets.

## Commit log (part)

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2025-08-08 Some converted to XML
2025-08-08 More converted
2025-08-13 Remove .gitmodules (no submodules exist)
2025-08-18 Some more converted to XML
2025-08-26 More conversions
2025-08-26 All converted
2025-08-26 Updating
2025-08-29 Added some panels
